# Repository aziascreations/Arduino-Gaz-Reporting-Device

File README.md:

# Title

## Warnings

## Project requirements

### School

### Personnal

Size (10*10.2 cm)

## Material List

## License

[Unlicense](LICENSE)

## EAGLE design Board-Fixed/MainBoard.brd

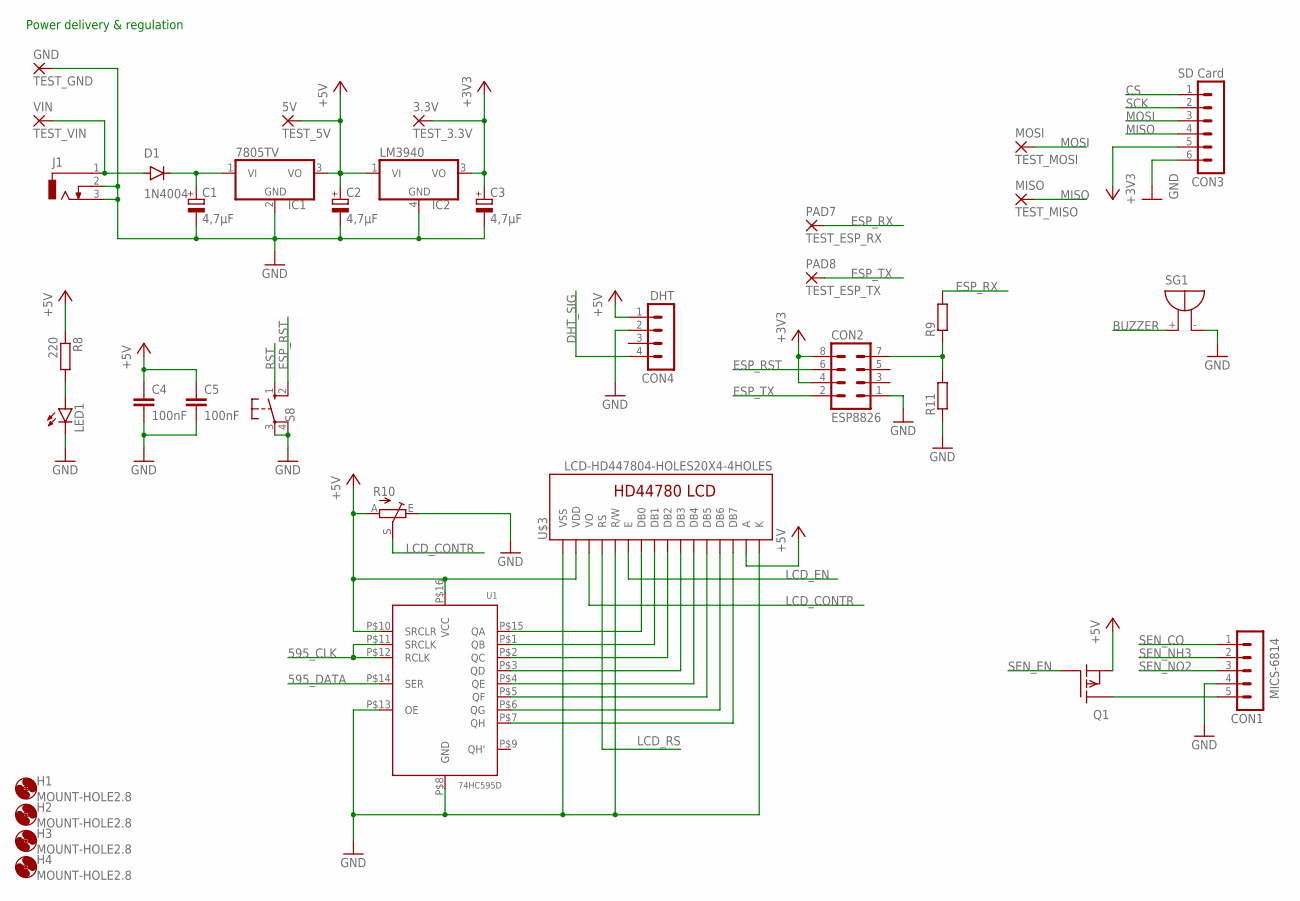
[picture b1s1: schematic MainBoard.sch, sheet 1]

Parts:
3.3V: TEST_3.3V; 2,54/0,9
5V: TEST_5V; 2,54/0,9
C1, C2, C3: 4,7µF; E2,5-6E
C4, C5: 100nF; C0805
CON1: MICS-6814; MA05-1
CON2: ESP8826; MA04-2
CON3: SD Card; MA06-1
CON4: DHT; MA04-1
D1: 1N4004; DO34-7
GND: TEST_GND; 2,54/0,9
H1, H2, H3, H4: MOUNT-HOLE2.8; 2,8
IC1: 7805TV; TO220V
IC2: LM3940; SOT223
J1: DCJ0303
LED1: LED3MM
MISO: TEST_MISO; 2,54/0,9
MOSI: TEST_MOSI; 2,54/0,9
PAD7: TEST_ESP_RX; 2,54/0,9
PAD8: TEST_ESP_TX; 2,54/0,9
Q1: LP0701N3; TO-92
R8: 220; 0204/7
R9, R11: R-EU_M0805; M0805
R10: TRIM_EU-RJ9W; RJ9W
S8: 10-XX; B3F-10XX
SG1: F/TMB
U1: 74HC595D; SOP-16
U$3: LCD-HD447804-HOLES20X4-4HOLES; LCD-20X4-4HOLES
VIN: TEST_VIN; 2,54/0,9

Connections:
595_CLK: U1.P$11 (SRCLK), U1.P$12 (RCLK); also elsewhere on the board
595_DATA: U1.P$14 (SER); also elsewhere on the board
+3V3: 3.3V.1, C3.+, CON2.4, CON2.8, CON3.5, IC2.3 (VO)
+5V: 5V.1, C2.+, C4.1, C5.1, CON4.1, IC1.3 (VO), IC2.1 (VI), Q1.1 (S), R8.1, R10.A, U1.P$10 (SRCLR), U1.P$16 (VCC), U$3.P$2 (VDD), U$3.P$15 (A); also elsewhere on the board
BUZZER: SG1.+; also elsewhere on the board
CS: CON3.1; also elsewhere on the board
DHT_SIG: CON4.4; also elsewhere on the board
ESP_RST: CON2.6, S8.2 (S1)
ESP_RX: PAD7.1, R9.2; also elsewhere on the board
ESP_TX: CON2.2, PAD8.1; also elsewhere on the board
GND: C1.-, C2.-, C3.-, C4.2, C5.2, CON1.4, CON2.1, CON3.6, CON4.2, GND.1, IC1.2 (GND), IC2.4 (GND), J1.2, J1.3, LED1.K (C), R10.E, R11.1, S8.3, S8.4 (P1), SG1.-, U1.P$8 (GND), U1.P$13 (OE), U$3.P$1 (VSS), U$3.P$5 (R/W), U$3.P$16 (K); also elsewhere on the board
LCD_CONTR: R10.S, U$3.P$3 (VO)
LCD_EN: U$3.P$6 (E); also elsewhere on the board
LCD_RS: U$3.P$4 (RS); also elsewhere on the board
MISO: CON3.4, MISO.1; also elsewhere on the board
MOSI: CON3.3, MOSI.1; also elsewhere on the board
unnamed: LED1.A, R8.2
unnamed: CON2.7, R9.1, R11.2
unnamed: U1.P$15 (QA), U$3.P$7 (DB0)
unnamed: U1.P$1 (QB), U$3.P$8 (DB1)
unnamed: U1.P$2 (QC), U$3.P$9 (DB2)
unnamed: U1.P$3 (QD), U$3.P$10 (DB3)
unnamed: U1.P$4 (QE), U$3.P$11 (DB4)
unnamed: U1.P$5 (QF), U$3.P$12 (DB5)
unnamed: U1.P$6 (QG), U$3.P$13 (DB6)
unnamed: U1.P$7 (QH), U$3.P$14 (DB7)
unnamed: D1.A, J1.1, VIN.1
unnamed: C1.+, D1.C, IC1.1 (VI)
unnamed: CON1.5, Q1.3 (D)
RST: S8.1 (S); also elsewhere on the board
SCK: CON3.2; also elsewhere on the board
SEN_CO: CON1.1; also elsewhere on the board
SEN_EN: Q1.2 (G); also elsewhere on the board
SEN_NH3: CON1.2; also elsewhere on the board
SEN_NO2: CON1.3; also elsewhere on the board

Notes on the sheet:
Power delivery & regulation

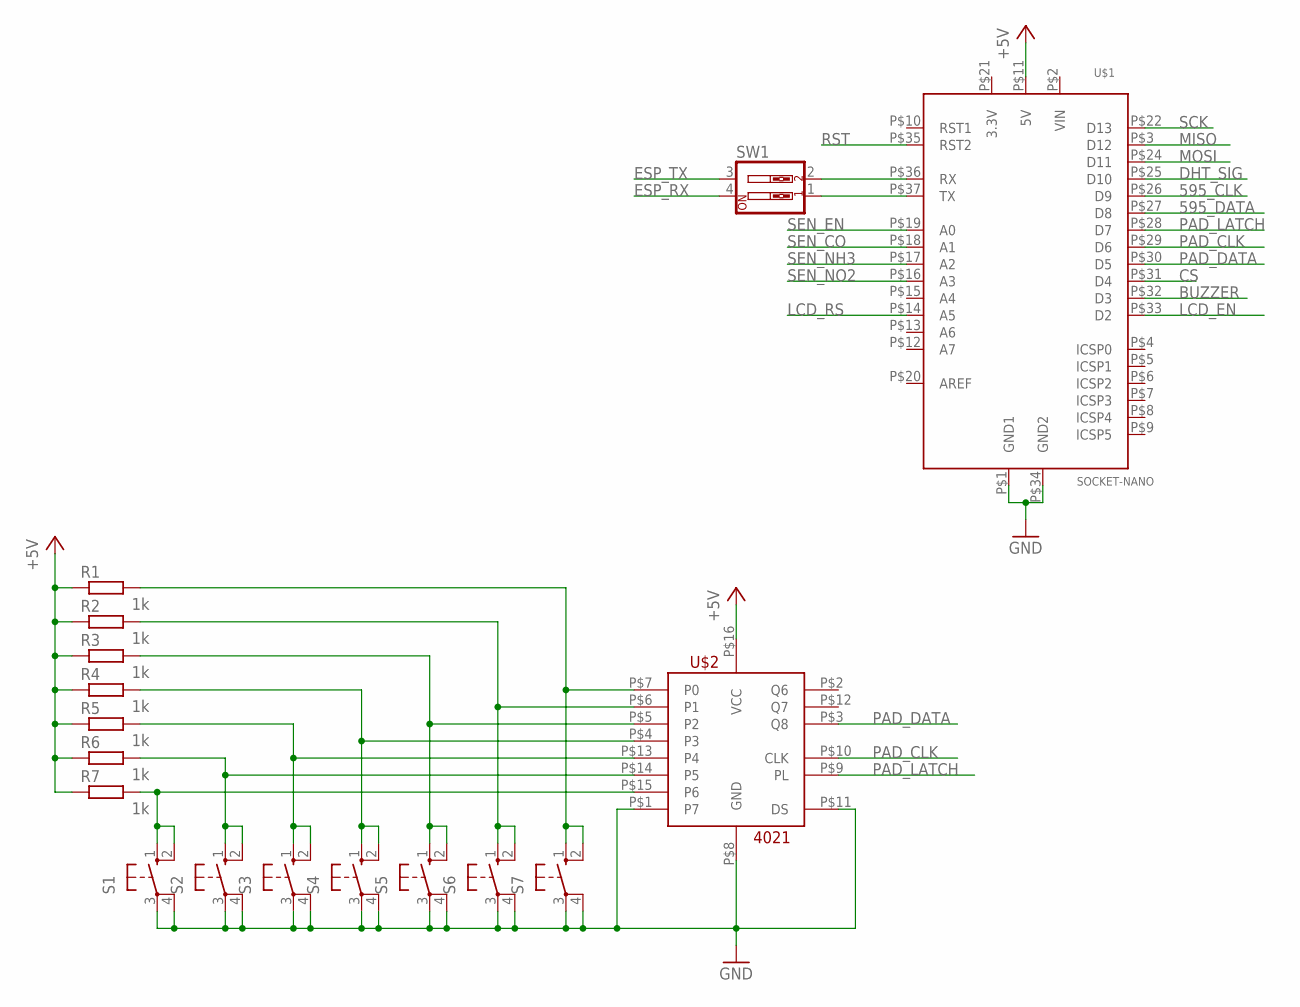
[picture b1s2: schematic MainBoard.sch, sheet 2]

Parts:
R1, R2, R3, R4, R5, R6, R7: 1k; 0204/7
S1, S2, S3, S4, S5, S6, S7: 10-XX; B3F-10XX
SW1: SW_DIP-2; EDG-02
U$1: SOCKET-NANO
U$2: 4021; DIP

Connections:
3.3V: U$1.P$21 (3.3V)
595_CLK: U$1.P$26 (D9); also elsewhere on the board
595_DATA: U$1.P$27 (D8); also elsewhere on the board
+5V: R1.1, R2.1, R3.1, R4.1, R5.1, R6.1, R7.1, U$1.P$11 (5V), U$2.P$16 (VCC); also elsewhere on the board
BUZZER: U$1.P$32 (D3); also elsewhere on the board
CS: U$1.P$31 (D4); also elsewhere on the board
DHT_SIG: U$1.P$25 (D10); also elsewhere on the board
ESP_RX: SW1.4; also elsewhere on the board
ESP_TX: SW1.3; also elsewhere on the board
GND: S1.3, S1.4 (P1), S2.3, S2.4 (P1), S3.3, S3.4 (P1), S4.3, S4.4 (P1), S5.3, S5.4 (P1), S6.3, S6.4 (P1), S7.3, S7.4 (P1), U$1.P$1 (GND1), U$1.P$34 (GND2), U$2.P$1 (P7), U$2.P$8 (GND), U$2.P$11 (DS); also elsewhere on the board
LCD_EN: U$1.P$33 (D2); also elsewhere on the board
LCD_RS: U$1.P$14 (A5); also elsewhere on the board
MISO: U$1.P$3 (D12); also elsewhere on the board
MOSI: U$1.P$24 (D11); also elsewhere on the board
unnamed: R7.2, S1.1 (S), S1.2 (S1), U$2.P$15 (P6)
unnamed: R6.2, S2.1 (S), S2.2 (S1), U$2.P$14 (P5)
unnamed: R5.2, S3.1 (S), S3.2 (S1), U$2.P$13 (P4)
unnamed: R4.2, S4.1 (S), S4.2 (S1), U$2.P$4 (P3)
unnamed: R3.2, S5.1 (S), S5.2 (S1), U$2.P$5 (P2)
unnamed: R2.2, S6.1 (S), S6.2 (S1), U$2.P$6 (P1)
unnamed: R1.2, S7.1 (S), S7.2 (S1), U$2.P$7 (P0)
unnamed: SW1.2, U$1.P$36 (RX)
unnamed: SW1.1, U$1.P$37 (TX)
PAD_CLK: U$1.P$29 (D6), U$2.P$10 (CLK)
PAD_DATA: U$1.P$30 (D5), U$2.P$3 (Q8)
PAD_LATCH: U$1.P$28 (D7), U$2.P$9 (PL)
RST: U$1.P$35 (RST2); also elsewhere on the board
SCK: U$1.P$22 (D13); also elsewhere on the board
SEN_CO: U$1.P$18 (A1); also elsewhere on the board
SEN_EN: U$1.P$19 (A0); also elsewhere on the board
SEN_NH3: U$1.P$17 (A2); also elsewhere on the board
SEN_NO2: U$1.P$16 (A3); also elsewhere on the board
VIN: U$1.P$2 (VIN)

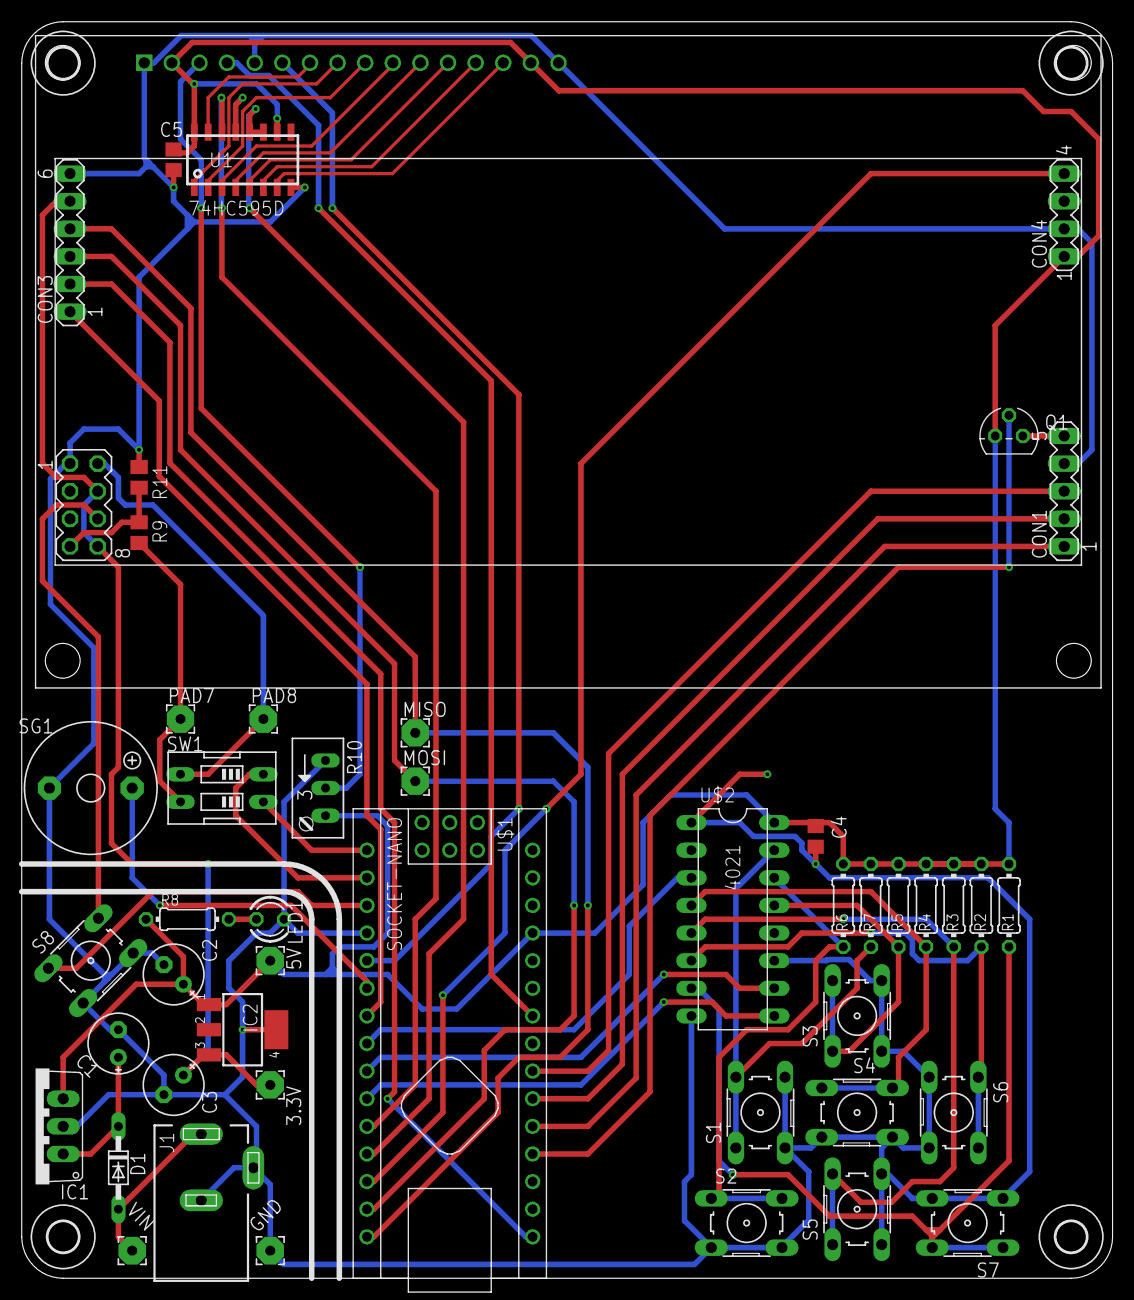
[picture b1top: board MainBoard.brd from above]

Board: 2 copper layers, 100.3 x 115.6 mm, 52 parts (0 on the bottom side), 47 nets.

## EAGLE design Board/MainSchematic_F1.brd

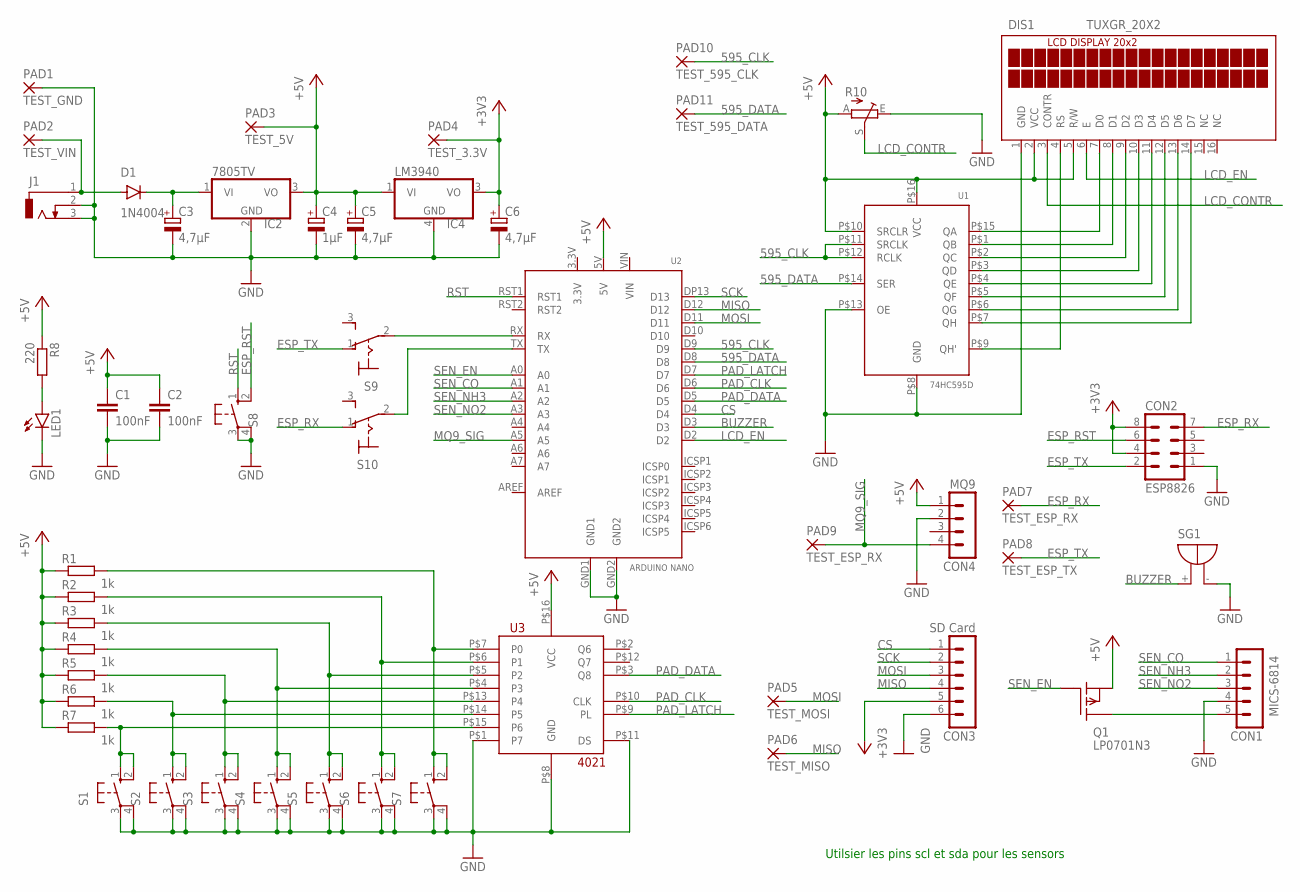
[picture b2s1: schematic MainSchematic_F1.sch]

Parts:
C1, C2: 100nF; C5B2.5
C3, C5, C6: 4,7µF; E2,5-6E
C4: 1µF; E2,5-6E
CON1: MICS-6814; MA05-1
CON2: ESP8826; MA04-2
CON3: SD Card; MA06-1
CON4: MQ9; MA04-1
D1: 1N4004; DO41-10
DIS1: TUXGR_20X2
IC2: 7805TV; TO220V
IC4: LM3940; SOT223
J1: DCJ0303
LED1: LED3MM
PAD1: TEST_GND; 2,54/0,9
PAD2: TEST_VIN; 2,54/0,9
PAD3: TEST_5V; 2,54/0,9
PAD4: TEST_3.3V; 2,54/0,9
PAD5: TEST_MOSI; 2,54/0,9
PAD6: TEST_MISO; 2,54/0,9
PAD7, PAD9: TEST_ESP_RX; 2,54/0,9
PAD8: TEST_ESP_TX; 2,54/0,9
PAD10: TEST_595_CLK; 2,54/0,9
PAD11: TEST_595_DATA; 2,54/0,9
Q1: LP0701N3; TO-92
R1, R2, R3, R4, R5, R6, R7: 1k; 0204/7
R8: 220; 0204/7
R10: TRIM_EU-RJ9W; RJ9W
S1, S2, S3, S4, S5, S6, S7, S8: 10-XX; B3F-10XX
S9, S10: 320-916
SG1: F/TMB
U1: 74HC595D; SOP-16
U2: ARDUINO NANO; SOCKET_NANO
U3: 4021; DIP

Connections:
3.3V: U2.3.3V
595_CLK: PAD10.1, U1.P$11 (SRCLK), U1.P$12 (RCLK), U2.D9
595_DATA: PAD11.1, U1.P$14 (SER), U2.D8
+3V3: C6.+, CON2.4, CON2.8, CON3.5, IC4.3 (VO), PAD4.1
+5V: C1.1, C2.1, C4.+, C5.+, CON4.1, DIS1.2 (VCC), DIS1.5 (R/W), IC2.3 (VO), IC4.1 (VI), PAD3.1, Q1.1 (S), R1.1, R2.1, R3.1, R4.1, R5.1, R6.1, R7.1, R8.1, R10.A, U1.P$10 (SRCLR), U1.P$16 (VCC), U2.5V, U3.P$16 (VCC)
BUZZER: SG1.+, U2.D3
CS: CON3.1, U2.D4
ESP_RST: CON2.6, S8.2 (S1)
ESP_RX: CON2.7, PAD7.1, S10.1 (O)
ESP_TX: CON2.2, PAD8.1, S9.1 (O)
GND: C1.2, C2.2, C3.-, C4.-, C5.-, C6.-, CON1.4, CON2.1, CON3.6, CON4.2, DIS1.1 (GND), IC2.2 (GND), IC4.4 (GND), J1.2, J1.3, LED1.K (C), PAD1.1, R10.E, S1.3, S1.4 (P1), S2.3, S2.4 (P1), S3.3, S3.4 (P1), S4.3, S4.4 (P1), S5.3, S5.4 (P1), S6.3, S6.4 (P1), S7.3, S7.4 (P1), S8.3, S8.4 (P1), SG1.-, U1.P$8 (GND), U1.P$13 (OE), U2.GND1, U2.GND2, U3.P$1 (P7), U3.P$8 (GND), U3.P$11 (DS)
LCD_CONTR: DIS1.3 (CONTR), R10.S
LCD_EN: DIS1.6 (E), U2.D2
MISO: CON3.4, PAD6.1, U2.D12
MOSI: CON3.3, PAD5.1, U2.D11
MQ9_SIG: CON4.4, PAD9.1, U2.A5
unnamed: LED1.A, R8.2
unnamed: DIS1.7 (D0), U1.P$15 (QA)
unnamed: DIS1.8 (D1), U1.P$1 (QB)
unnamed: DIS1.9 (D2), U1.P$2 (QC)
unnamed: DIS1.10 (D3), U1.P$3 (QD)
unnamed: DIS1.11 (D4), U1.P$4 (QE)
unnamed: DIS1.12 (D5), U1.P$5 (QF)
unnamed: DIS1.13 (D6), U1.P$6 (QG)
unnamed: DIS1.14 (D7), U1.P$7 (QH)
unnamed: R7.2, S1.1 (S), S1.2 (S1), U3.P$15 (P6)
unnamed: DIS1.4 (RS), U1.P$9 (QH')
unnamed: R6.2, S2.1 (S), S2.2 (S1), U3.P$14 (P5)
unnamed: R5.2, S3.1 (S), S3.2 (S1), U3.P$13 (P4)
unnamed: R4.2, S4.1 (S), S4.2 (S1), U3.P$4 (P3)
unnamed: R3.2, S5.1 (S), S5.2 (S1), U3.P$5 (P2)
unnamed: R2.2, S6.1 (S), S6.2 (S1), U3.P$6 (P1)
unnamed: R1.2, S7.1 (S), S7.2 (S1), U3.P$7 (P0)
unnamed: D1.A, J1.1, PAD2.1
unnamed: C3.+, D1.C, IC2.1 (VI)
unnamed: S9.2, U2.RX
unnamed: S10.2, U2.TX
unnamed: CON1.5, Q1.3 (D)
PAD_CLK: U2.D6, U3.P$10 (CLK)
PAD_DATA: U2.D5, U3.P$3 (Q8)
PAD_LATCH: U2.D7, U3.P$9 (PL)
RST: S8.1 (S), U2.RST1
SCK: CON3.2, U2.DP13 (D13)
SEN_CO: CON1.1, U2.A1
SEN_EN: Q1.2 (G), U2.A0
SEN_NH3: CON1.2, U2.A2
SEN_NO2: CON1.3, U2.A3
VIN: U2.VIN

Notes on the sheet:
Utilsier les pins scl et sda pour les sensors

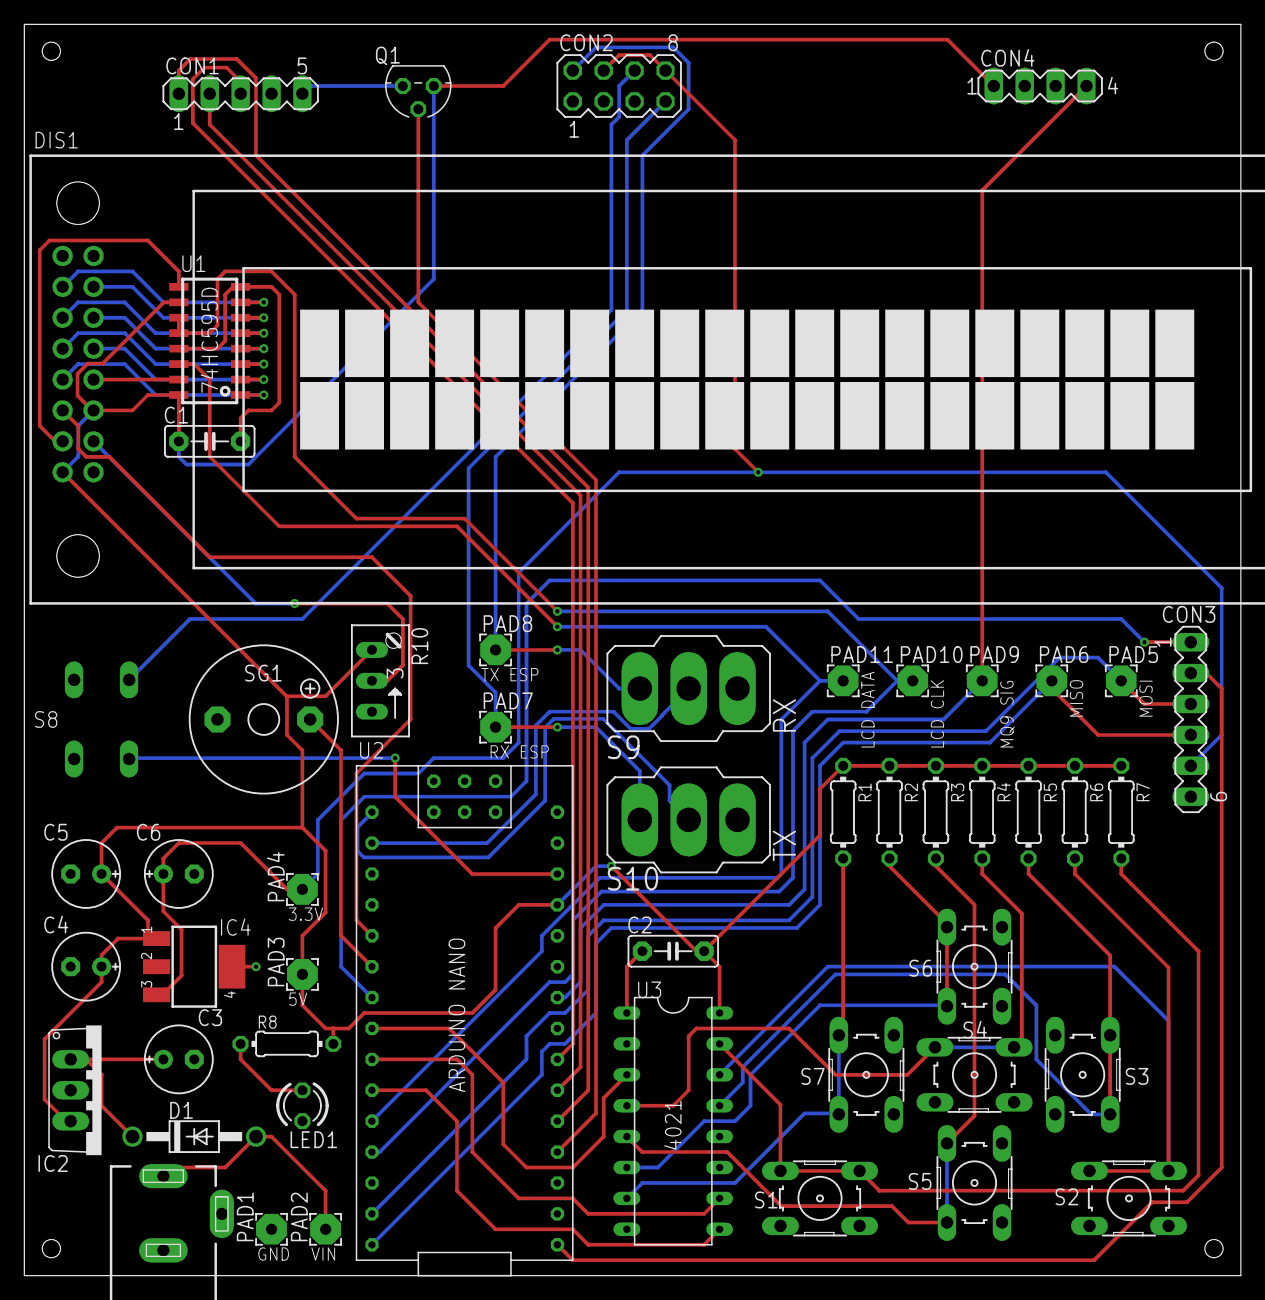
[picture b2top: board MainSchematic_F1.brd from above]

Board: 2 copper layers, 100.0 x 102.9 mm, 51 parts (1 on the bottom side), 46 nets.

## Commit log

2020-04-30 Moved .ino files to Arduino/
2020-04-30 Updated PB-Utils to the latest commit
2020-05-02 Added LCD basic functions and improved menu basic function
2020-05-02 Improved menu and added placeholders for ESP, logger, config and sensors
2020-05-04 Finished logging base and template PB client
2020-05-24 Added Basic ESP code and updated some sensor and LCD code
    Added placeholder for DHT
    Changed LCD register pin
2020-05-24 Cleaned some code in the ESP and LCD and added packet support
2020-05-30 Added new board and packet related code
2020-05-30 Finished new board and added some missing stuff
2021-06-29 Update .gitignore, 4021.lbr, and 29 more files...
